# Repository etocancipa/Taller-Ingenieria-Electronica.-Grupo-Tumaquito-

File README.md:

# Taller-Ingenieria-Electronica.-Grupo-Tumaquito-
Este sera el repositorio del grupo "Tumaquito". Aqui se registraran la documentación y avances en el proyecto.

## LEER WIKI PARA DETALLES DEL PROYECTO

## Integrantes:
+Joseph Reyes

+Jose Dario

+Luis Cortes

+Eddy Tocancipa

+Helen Hernandez

+Sebastian Vanegas

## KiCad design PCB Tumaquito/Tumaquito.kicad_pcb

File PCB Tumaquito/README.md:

# ARCHIVOS PCB TUMAQUITO:

Aqui puedes encontrar la totalidad de los archivos que fueron utilizados para la creción de la PCB de Tumaquito!

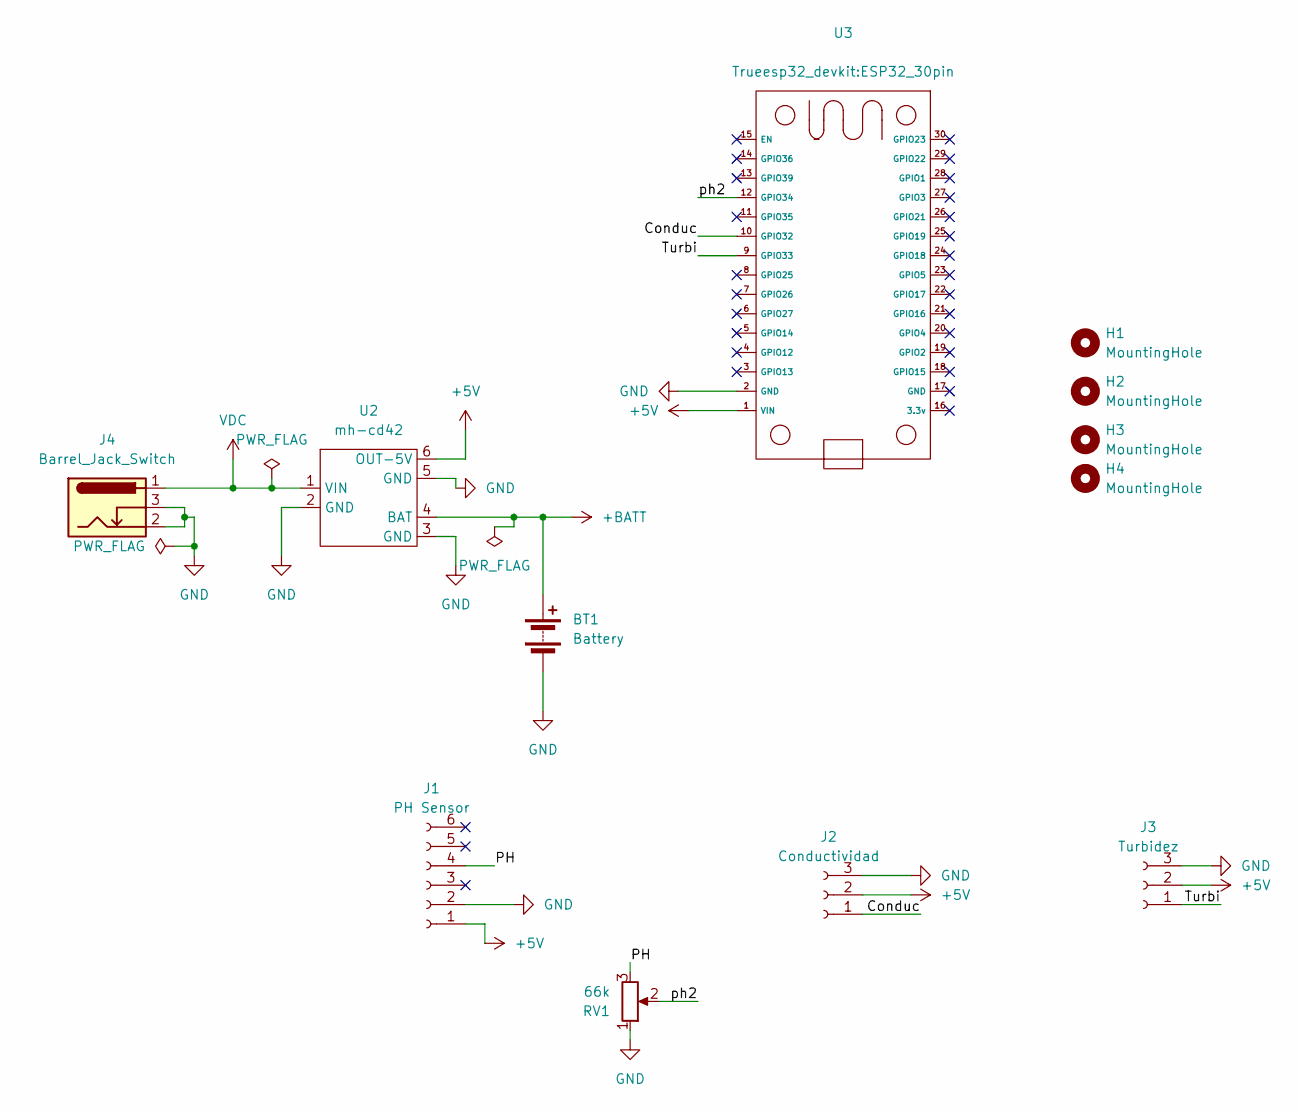
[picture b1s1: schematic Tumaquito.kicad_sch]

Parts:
BT1: Battery; BatteryHolder_Keystone_1042_1x18650
H1, H2, H3, H4: MountingHole; MountingHole_3.2mm_M3
J1: PH Sensor; PinSocket_1x06_P2.54mm_Vertical
J2: Conductividad; PinSocket_1x03_P2.54mm_Vertical
J3: Turbidez; PinSocket_1x03_P2.54mm_Vertical
J4: Barrel_Jack_Switch; BarrelJack_Horizontal
RV1: 66k; Potentiometer_Piher_T-16H_Single_Horizontal
U2: mh-cd42
U3: ESP32_30pin

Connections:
+5V: J1.1, J2.2, J3.2, U2.6 (OUT-5V), U3.1 (VIN)
+BATT: BT1.1 (+), U2.4 (BAT)
/Conduc: J2.1, U3.10 (GPIO32)
/PH: J1.4, RV1.3
/Turbi: J3.1, U3.9 (GPIO33)
/ph2: RV1.2, U3.12 (GPIO34)
GND: BT1.2 (-), J1.2, J2.3, J3.3, J4.2, J4.3, RV1.1, U2.2 (GND), U2.3 (GND), U2.5 (GND), U3.2 (GND)
VDC: J4.1, U2.1 (VIN)

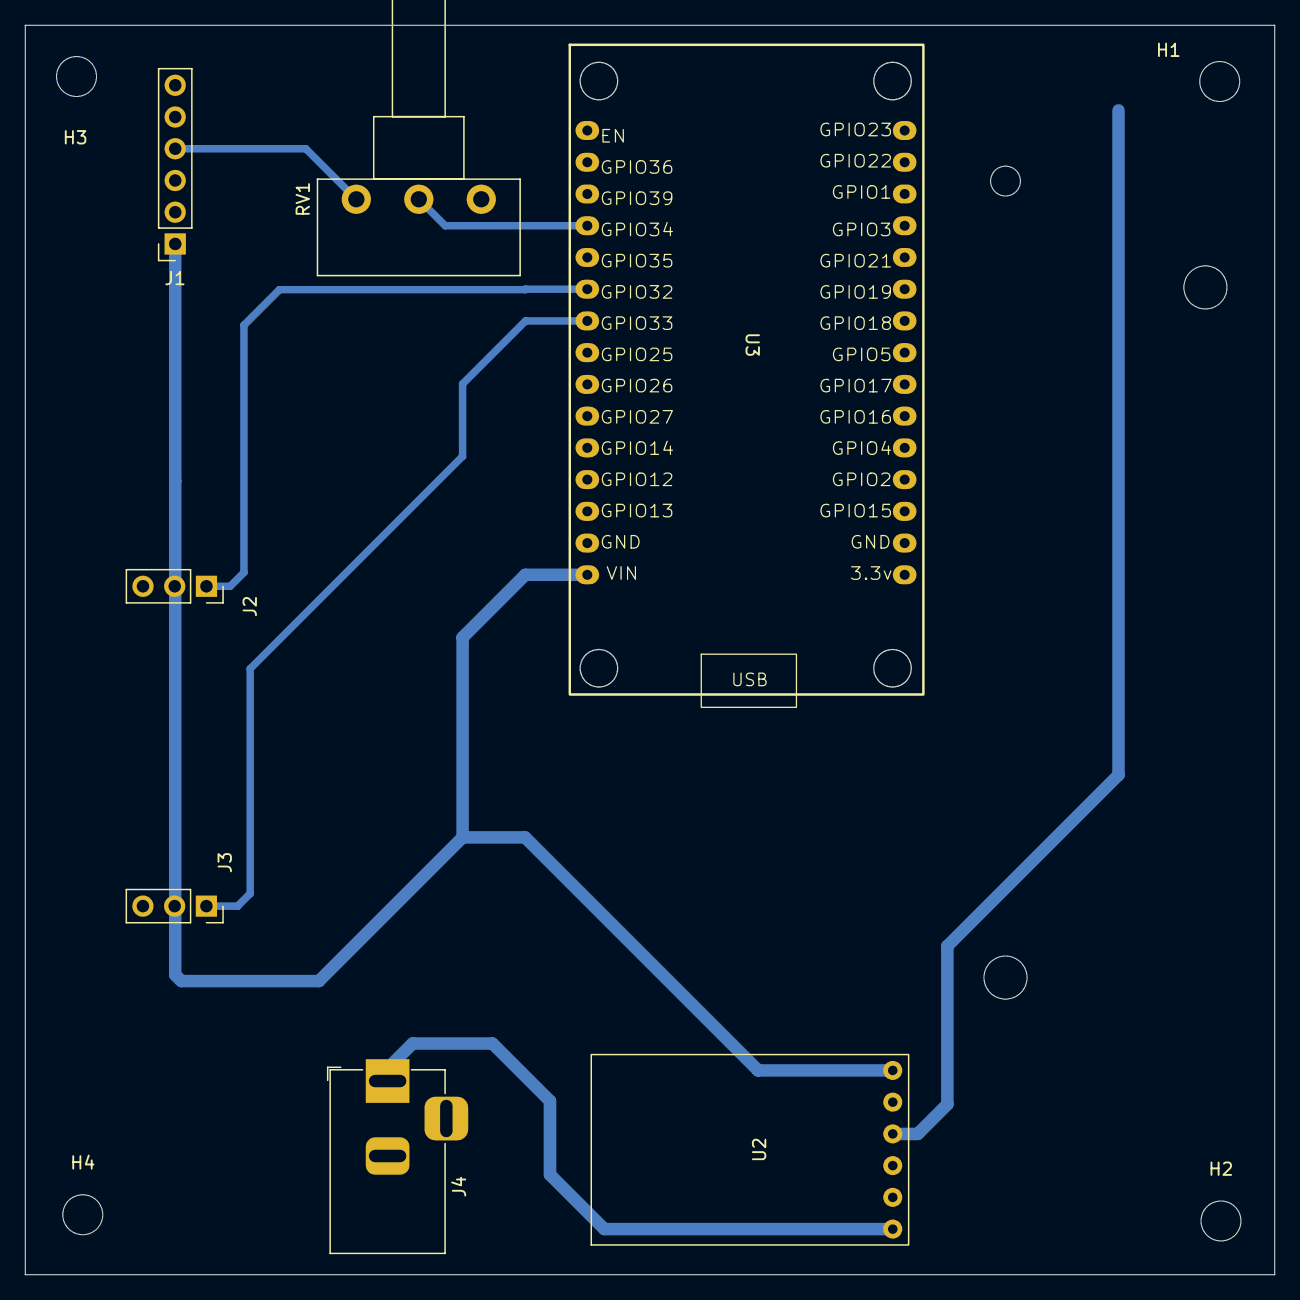
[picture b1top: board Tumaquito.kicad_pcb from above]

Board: 2 copper layers, 100.0 x 100.0 mm, 12 parts (1 on the bottom side), 8 nets.

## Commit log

2025-10-30 Create d
2025-10-30 Create a
2025-11-19 Create Dawdasdad
2025-12-11 PCB Update
2025-12-11 Adding the 2 last folders
2025-12-11 Additional changes to the 2 extra fodlers
2025-12-13 last changes to code
